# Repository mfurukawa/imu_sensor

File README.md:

# imu_sensor
Eagle PCB, mbed source code included.

- September 9, 2020 - changed Python code and mbed Protocol / Yuto Nakayachi 
- July  3, 2020 - Python, Unity, C# sample added / Masahiro Furukawa
- June 26, 2020 - created / Masahiro Furukawa

Masahiro Furukawa / Yuto Nakayachi

# mbed Protocol 

# for 4Ch MPU-9250 Sensor Module 

mbed Source Code

https://os.mbed.com/users/nakataniuchi/code/MPU9250_CH4_3_0_0/

see main.cpp

https://os.mbed.com/users/nakataniuchi/code/MPU9250_CH4_3_0_0//file/cdeed96f97fc/main.cpp/

# How to check mbed response

1. Open terminal software.
2. Set baudrate as 921600bps.
3. Set linefeed as “LF” only.
4. Press reset button on mbed.
5. If you see some message, mbed works.
6. Press ‘s’ key and you will see the data stream
7. Press ‘r’ key and it will stop.

# Protocol for ver 3.0.0

Byte order is **Big** Endian

for Header : 1 bytes = 8 bits describes 1 value 

<td>*</td> : header 

for Acceleration  : 2 bytes = 16 bits describes 1 value

Higher Byte 

A<sub>x, i</sub> : acceleration on axis X of ch i

A<sub>y, i</sub> : acceleration on axis Y of ch i 

A<sub>z, i</sub> : acceleration on axis Y of ch i 

Lower Byte

a<sub>x, i</sub> : acceleration on axis X of ch i 

a<sub>y, i</sub> : acceleration on axis Y of ch i 

a<sub>z, i</sub> : acceleration on axis Z of ch i 

for Angular Velocity  : 2 bytes = 16 bits describes 1 value

Higher Byte

W<sub>x, i</sub> : angular velocity on axis X of ch i 

W<sub>y, i</sub> : angular velocity on axis Y of ch i 

W<sub>z, i</sub> : angular velocity on axis Z of ch i 

Lower Byte

w<sub>x, i</sub> : angular velocity on axis X of ch i

w<sub>y, i</sub> : angular velocity on axis Y of ch i

w<sub>z, i</sub> : angular velocity on axis Z of ch i

Time : Time value gives the difference from the previous sequence

Byte Array (52 Bytes = 1 Byte(Header) + 2 Byte * 3(xyz) *2(Acc, Gyro) * 4 (Ch) + 1 Byte(Time value) + 2 Byte(CR, LF) ) :

<table>
  <tr>
   <td>0
   </td>
   <td>1
   </td>
   <td>2
   </td>
   <td>3
   </td>
   <td>4
   </td>
   <td>5
   </td>
   <td>6
   </td>
   <td>7
   </td>
   <td>8
   </td>
   <td>9
   </td>
   <td>10
   </td>
   <td>11
   </td>
   <td>12
   </td>
   <td>13
   </td>
   <td>14
   </td>
   <td>15
   </td>
  </tr>
  <tr>
   <td>*
   </td>
   <td>
   </td>
   <td>
   </td>
   <td>
   </td>
   <td>
   </td>
   <td>
   </td>
   <td>
   </td>
   <td>
   </td>
   <td>
   </td>
   <td>
   </td>
   <td>
   </td>
   <td>
   </td>
   <td>
   </td>
   <td>
   </td>
   <td>
   </td>
   <td>
   </td>
  <tr>
   <td>A<sub>x,1</sub> 
   </td>
   <td>a<sub>x,1</sub> 
   </td>
   <td>A<sub>y,1</sub> 
   </td>
   <td>a<sub>y,1</sub> 
   </td>
   <td>A<sub>z,1</sub> 
   </td>
   <td>a<sub>z,1</sub> 
   </td>
   <td>W<sub>x,1</sub> 
   </td>
   <td>w<sub>x,1</sub>
   </td>
   <td>W<sub>y,1</sub>
   </td>
   <td>w<sub>y,1</sub>
   </td>
   <td>W<sub>z,1</sub> 
   </td>
   <td>w<sub>z,1</sub> 
   </td>
   <td>A<sub>x,<em>2 </em></sub>
   </td>
   <td>a<sub>x,<em>2 </em></sub>
   </td>
   <td>A<sub>y,<em>2 </em></sub>
   </td>
   <td>a<sub>y,<em>2 </em></sub>
   </td>
  </tr>
  <tr>
   <td>A<sub>z,<em>2</em></sub>
   </td>
   <td>a<sub>z,<em>2</em></sub>
   </td>
   <td>W<sub>x,<em>2</em></sub>
   </td>
   <td>w<sub>x,<em>2</em></sub>
   </td>
   <td>W<sub>y,<em>2</em></sub>
   </td>
   <td>w<sub>y,<em>2</em></sub>
   </td>
   <td>W<sub>z,2</sub>
   </td>
   <td>w<sub>z,2</sub>
   </td>
   <td>A<sub>x,3</sub>
   </td>
   <td>a<sub>x,3</sub>
   </td>
   <td>A<sub>y,3</sub>
   </td>
   <td>a<sub>y,3</sub>
   </td>
   <td>A<sub>z,3</sub>
   </td>
   <td>a<sub>z,3</sub>
   </td>
   <td>W<sub>x,3</sub>
   </td>
   <td>w<sub>x,3</sub>
   </td>
  </tr>
  <tr>
   <td>W<sub>y,3</sub>
   </td>
   <td>w<sub>y,3</sub>
   </td>
   <td>W<sub>z,3</sub> 
   </td>
   <td>w<sub>z,3</sub>
   </td>
   <td>A<sub>x,<em>4</em></sub>
   </td>
   <td>a<sub>x,<em>4</em></sub>
   </td>
   <td>A<sub>y,<em>4</em></sub>
   </td>
   <td>a<sub>y,<em>4</em></sub>
   </td>
   <td>A<sub>z,4</sub> 
   </td>
   <td>a<sub>z,4</sub>
   </td>
   <td>W<sub>x,4</sub> 
   </td>
   <td>w<sub>x,4</sub>
   </td>
   <td>W<sub>y,4</sub>
   </td>
   <td>w<sub>y,4</sub>
   </td>
   <td>W<sub>z,4</sub>
   </td>
   <td>w<sub>z,4</sub> 
   </td>
  </tr>
  <tr>
   <td>Time
   </td>
   <td>CR
   </td>
   <td>LF
   </td>
   <td>
   </td>
   <td>
   </td>
   <td>
   </td>
   <td>
   </td>
   <td>
   </td>
   <td>
   </td>
   <td>
   </td>
   <td>
   </td>
   <td>
   </td>
   <td>
   </td>
   <td>
   </td>
   <td>
   </td>
   <td>
   </td>
  </tr>
</table>

## MPU9250.h

16bits(= 2 Bytes) represents one value. Angular velocity represents in the same way. The address below shows data address in MPU-9250 IMU sensor.

> ```
> #define MPUREG_ACCEL_XOUT_H 0x3B
> #define MPUREG_ACCEL_XOUT_L 0x3C
> 
> #define MPUREG_ACCEL_YOUT_H 0x3D
> #define MPUREG_ACCEL_YOUT_L 0x3E
> 
> #define MPUREG_ACCEL_ZOUT_H 0x3F
> #define MPUREG_ACCEL_ZOUT_L 0x40
> 
> 
> #define MPUREG_GYRO_XOUT_H 0x43
> #define MPUREG_GYRO_XOUT_L 0x44
> 
> #define MPUREG_GYRO_YOUT_H 0x45
> #define MPUREG_GYRO_YOUT_L 0x46
> 
> #define MPUREG_GYRO_ZOUT_H 0x47
> #define MPUREG_GYRO_ZOUT_L 0x48
> ```

Thus six unsigned integer (8bit) variales represent three accelerations. Also six unsigned integer (8bit) variables represent three angular velocity. 

> ```
> uint8_t accelerometer_response[6]; 
> uint8_t gyroscope_response[6]; 
> ```

## MPU9250.cpp

> ```
> /*-----------------------------------------------------------------------------------------------
>                                 READ ACCELEROMETER
> usage: call this function to read accelerometer data. Axis represents selected axis:
> 0 -> X axis
> 1 -> Y axis
> > 2 -> Z axis
> 
> void mpu9250_spi::read_acc()
> {
>     //int16_t bit_data;
> //    float data;
> //    int i;
>     ReadRegs(MPUREG_ACCEL_XOUT_H,accelerometer_response,6);    
> //    for(i=0; i<3; i++) {
> //        bit_data=((int16_t)accelerometer_response[i*2]<<8)|accelerometer_response[i*2+1];
> //        data=(float)bit_data;
> //        accelerometer_data[i]=data/acc_divider;
> //        
> //    }
>     
> }
> ```

## main.cpp

> ```
> void eventFunc(void)
> {
>   ...
>     // set header 
>     putc(42,stdout); // * 
>
>     for(int i=0; i<nCh; i++) {
>         for(int j=0; j<6; j++) putc(imu[i]->accelerometer_response[j], stdout);
>         for(int j=0; j<6; j++) putc(imu[i]->gyroscope_response[j],     stdout);
>     }
>     tmp_time = sp_time.read_ms();
>     res_time = tmp_time - past_time;
>     past_time = tmp_time;
>     putc(res_time,stdout); //Time Value 
>     putc(13, stdout);  //0x0d = 13(10) CR（復帰）
>     putc(10, stdout);  //0x0a = 10(10) LF（改行）
> }
> ```

# References

## How to read byte stream with Python

[https://qiita.com/keitasumiya/items/25a707c37a73bfd95bac](https://qiita.com/keitasumiya/items/25a707c37a73bfd95bac)

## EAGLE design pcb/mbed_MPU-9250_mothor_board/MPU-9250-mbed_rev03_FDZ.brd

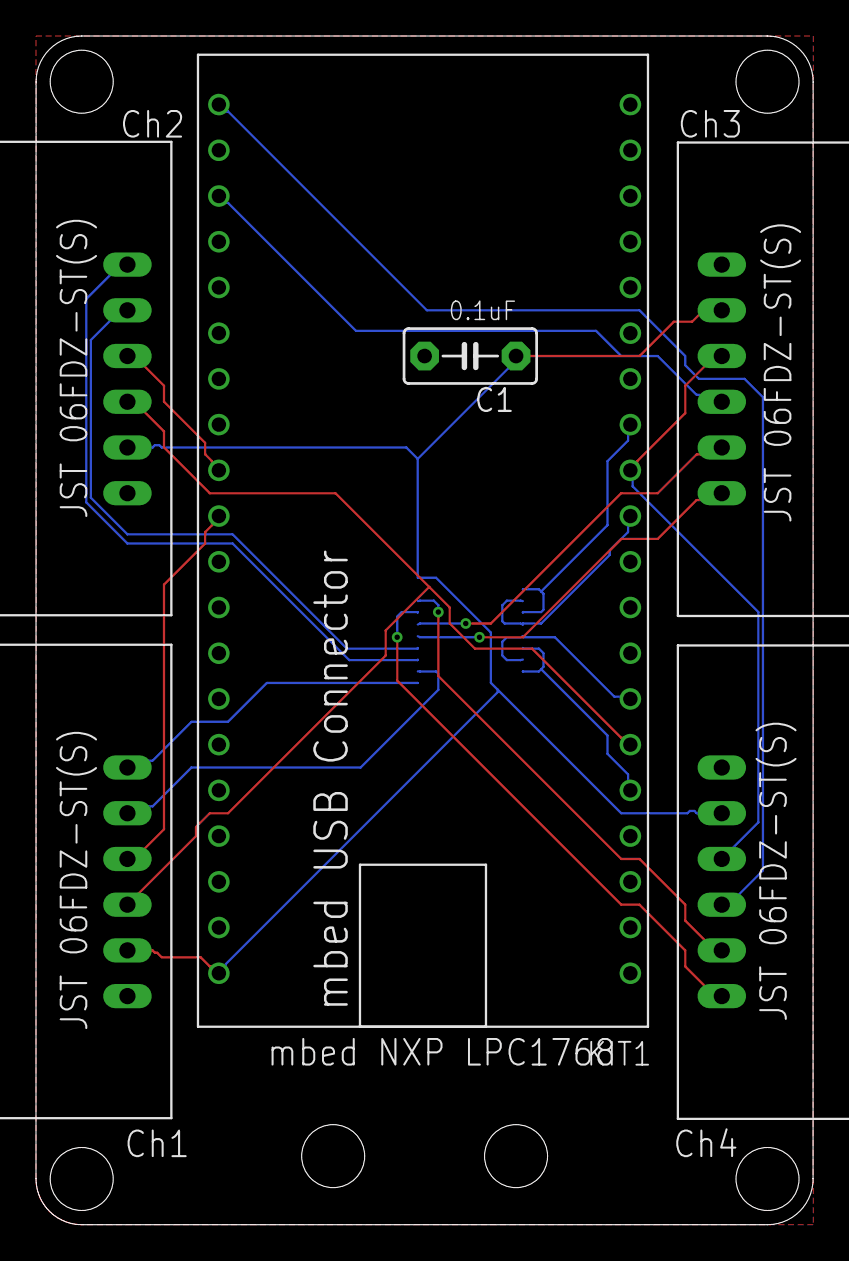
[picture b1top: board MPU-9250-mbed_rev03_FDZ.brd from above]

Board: 4 copper layers, 43.2 x 66.0 mm, 7 parts (1 on the bottom side), 20 nets.

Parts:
C1: 0.1u; C5B3
IC1: 74541PW; TSSOP20
KIT1: MBED_NXP_LPC1768; MBED-KIT
U$1, U$2, U$3, U$4: 06FDZ-ST(S)

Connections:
->CLK_SPI1->: IC1.6, IC1.8, KIT1.P$7
->CLK_SPI2->: IC1.2, IC1.4, KIT1.P$13
->MOSI_SPI1->: IC1.7, IC1.9, KIT1.P$5
->MOSI_SPI2->: IC1.3, IC1.5, KIT1.P$11
<-MISO_SPI1<-: KIT1.P$6, U$1.P$3, U$2.P$3
<-MISO_SPI2<-: KIT1.P$12, U$3.P$3, U$4.P$3
CON1_CLK_SPI1: IC1.12, U$1.P$5
CON1_MOSI_SPI1: IC1.11, U$1.P$6
CON2_CLK_SPI1: IC1.14, U$2.P$5
CON2_MOSI_SPI1: IC1.13, U$2.P$6
CON3_CLK_SPI2: IC1.16, U$3.P$5
CON3_MOSI_SPI2: IC1.15, U$3.P$6
CON4_CLK_SPI2: IC1.18, U$4.P$5
CON4_MOSI_SPI2: IC1.17, U$4.P$6
GND: C1.2, IC1.1, IC1.10, IC1.19, KIT1.GND, U$1.P$1, U$2.P$1, U$3.P$1, U$4.P$1
VDD: C1.1, IC1.20, KIT1.VOUT, U$1.P$2, U$2.P$2, U$3.P$2, U$4.P$2
~CS1: KIT1.P$30, U$1.P$4
~CS2: KIT1.P$29, U$2.P$4
~CS3: KIT1.P$23, U$3.P$4
~CS4: KIT1.P$21, U$4.P$4

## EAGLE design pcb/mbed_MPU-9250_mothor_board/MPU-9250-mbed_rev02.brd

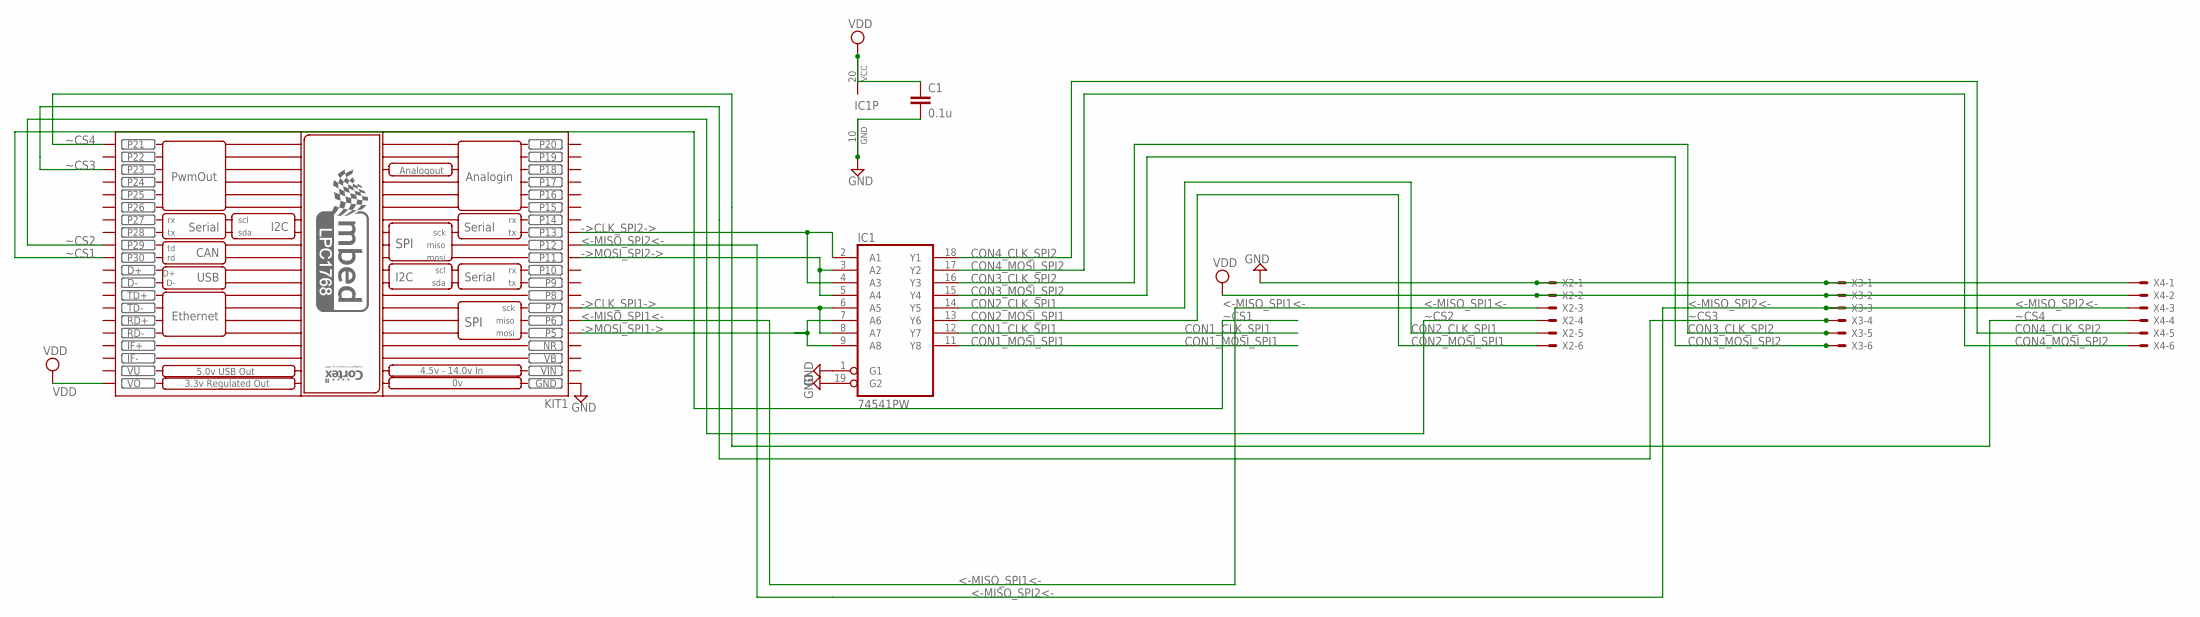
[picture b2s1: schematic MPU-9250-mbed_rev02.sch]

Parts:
C1: 0.1u; C5B3
IC1: 74541PW; TSSOP20
KIT1: MBED_NXP_LPC1768; MBED-KIT
X2, X3, X4: 22-23-2061

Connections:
->CLK_SPI1->: IC1.6 (A5), IC1.8 (A7), KIT1.P$7 (P7)
->CLK_SPI2->: IC1.2 (A1), IC1.4 (A3), KIT1.P$13 (P13)
->MOSI_SPI1->: IC1.7 (A6), IC1.9 (A8), KIT1.P$5 (P5)
->MOSI_SPI2->: IC1.3 (A2), IC1.5 (A4), KIT1.P$11 (P11)
<-MISO_SPI1<-: KIT1.P$6 (P6), X2.3
<-MISO_SPI2<-: KIT1.P$12 (P12), X3.3, X4.3
CON1_CLK_SPI1: IC1.12 (Y7)
CON1_MOSI_SPI1: IC1.11 (Y8)
CON2_CLK_SPI1: IC1.14 (Y5), X2.5
CON2_MOSI_SPI1: IC1.13 (Y6), X2.6
CON3_CLK_SPI2: IC1.16 (Y3), X3.5
CON3_MOSI_SPI2: IC1.15 (Y4), X3.6
CON4_CLK_SPI2: IC1.18 (Y1), X4.5
CON4_MOSI_SPI2: IC1.17 (Y2), X4.6
GND: C1.2, IC1.1 (G1), IC1.10 (GND), IC1.19 (G2), KIT1.GND, X2.1, X3.1, X4.1
NR: KIT1.NR
VB: KIT1.VB
VDD: C1.1, IC1.20 (VCC), KIT1.VOUT (VO), X2.2, X3.2, X4.2
VIN: KIT1.VIN
VU: KIT1.VU
~CS1: KIT1.P$30 (P30)
~CS2: KIT1.P$29 (P29), X2.4
~CS3: KIT1.P$23 (P23), X3.4
~CS4: KIT1.P$21 (P21), X4.4

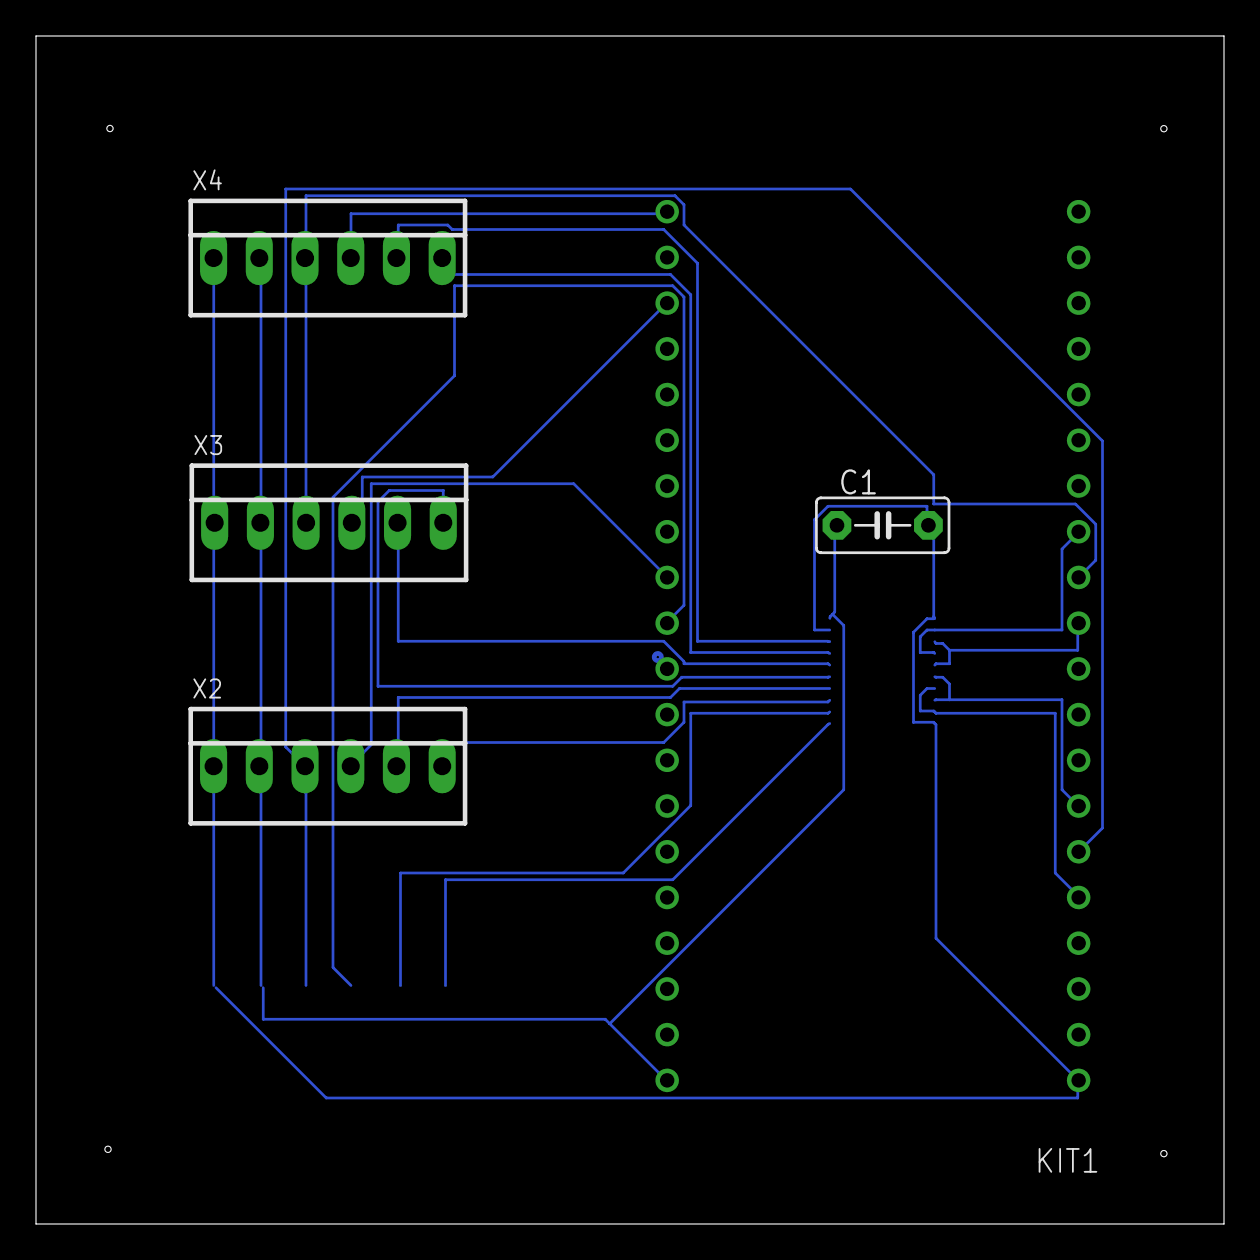
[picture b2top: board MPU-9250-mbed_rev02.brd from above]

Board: 2 copper layers, 66.0 x 66.0 mm, 6 parts (1 on the bottom side), 17 nets.

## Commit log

2020-06-30 modified .ignore
2020-06-30 python sample added
2020-06-30 transfer integer to real value
2020-07-02 (unstable) added C# sample
2020-07-03 added Unity sample
2020-07-03 updated .ignore
2020-07-08 Added ToDo
2020-07-29 added python Jupyter Note
2020-08-11 Colaboratory を使用して作成しました
2020-09-09 Update README.md
    CR-LFを読み出してから、50byte固定長を読み出し、その先頭バイトデータがheaderと一致しているか確認し、一致していれば格納、していなければやり直しという実装にしました。
    追加したheaderは1byteですがCR - LF - Headerと、3byte連続で一致する必要があるため、実質headerが3bytesあるのと同じ実装になります。
2020-09-11 binファイルとpythonファイルを変更しました。
    3つのファイルを追加しました。
    [binファイル]
    mbedのbinファイルを新しいものに変更しました。
    [read_acc_3_0_0.py]
    mbedから送られてくるbinaryデータを受け取り、それをcsvファイルにおとす関数です。
    binaryデータの受け取り方をreadline()関数からread()関数に変更し、1byteずつ読み込むことにしました。
2020-09-13 README.md, main.cppの追加とread_acc_3_0_0.pyの微修正
    [ README.md ]
    pythonファイルについてのREADME.mdをimu_sensor/src/pythonに追加しました。
    [ main.cpp ]
    mbedのmain.cppをimu_sensor/mbed/srcに追加しました。
    [ read_acc_3_0_0.py ]
    writeCSV()関数内で、作成するCSVファイルの名前がtest~.csvになっていたので、acc_data~.csvに変更しました。
2020-10-01 added acc calibration (under confirmation)
2020-10-01 Update visualize_acc_3_0_0.py
    ・縦軸の物理量の単位（Gとdps）を追加
    ・横軸の単位をmsからsに変更
2024-09-25 Sensor GUI with tkinter
    Designed by Masahiro Furukawa, Implemented by ChatGPT
2024-09-25 added Readme for PCB
2024-09-25 Added Break Signal Sending, Auto COM Port Scan
    Implemented by ChatGPT, Directed by Masahiro Furukawa
2024-09-25 Added Start/Stop func
2024-09-25 Status Monitor works
2024-09-25 big endien
    ToDo: Sampling Rate is too slow. Gyro Data is not stored.
2024-09-25 rev 1.0 stable 500Hz sampling done
2024-09-26 センサーの取り付けChによらず計測できるようにした
2024-09-26 minor update
2024-09-26 added combo box (not finished yet)
2024-09-27 added latest firmware
2024-10-01 MPU-9250-Ch1_ACC_GYRO_1kHz_20241001
2024-10-01 stable
2024-10-03 Added FFT function
2025-03-31 Added Two Channels Logger before revising
2025-03-31 added src/Python/read_acc_3_0_1_forWHC(2Ch).py
2025-03-31 Added mbed source
2025-03-31 before revising by ChatGPT 4o
2025-03-31 under construction
2025-03-31 update header
2025-03-31 unser const. succeeded serial receiving process.
2025-03-31 fixed byte decoder. must fix milli second
2025-03-31 added README.md for mbed
2025-03-31 stable revision
2025-04-01 added message function. stable revision
2025-04-01 move README.md
